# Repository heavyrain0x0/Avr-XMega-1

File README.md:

# Avr-XMega-1
An AVR Xmega Development Board

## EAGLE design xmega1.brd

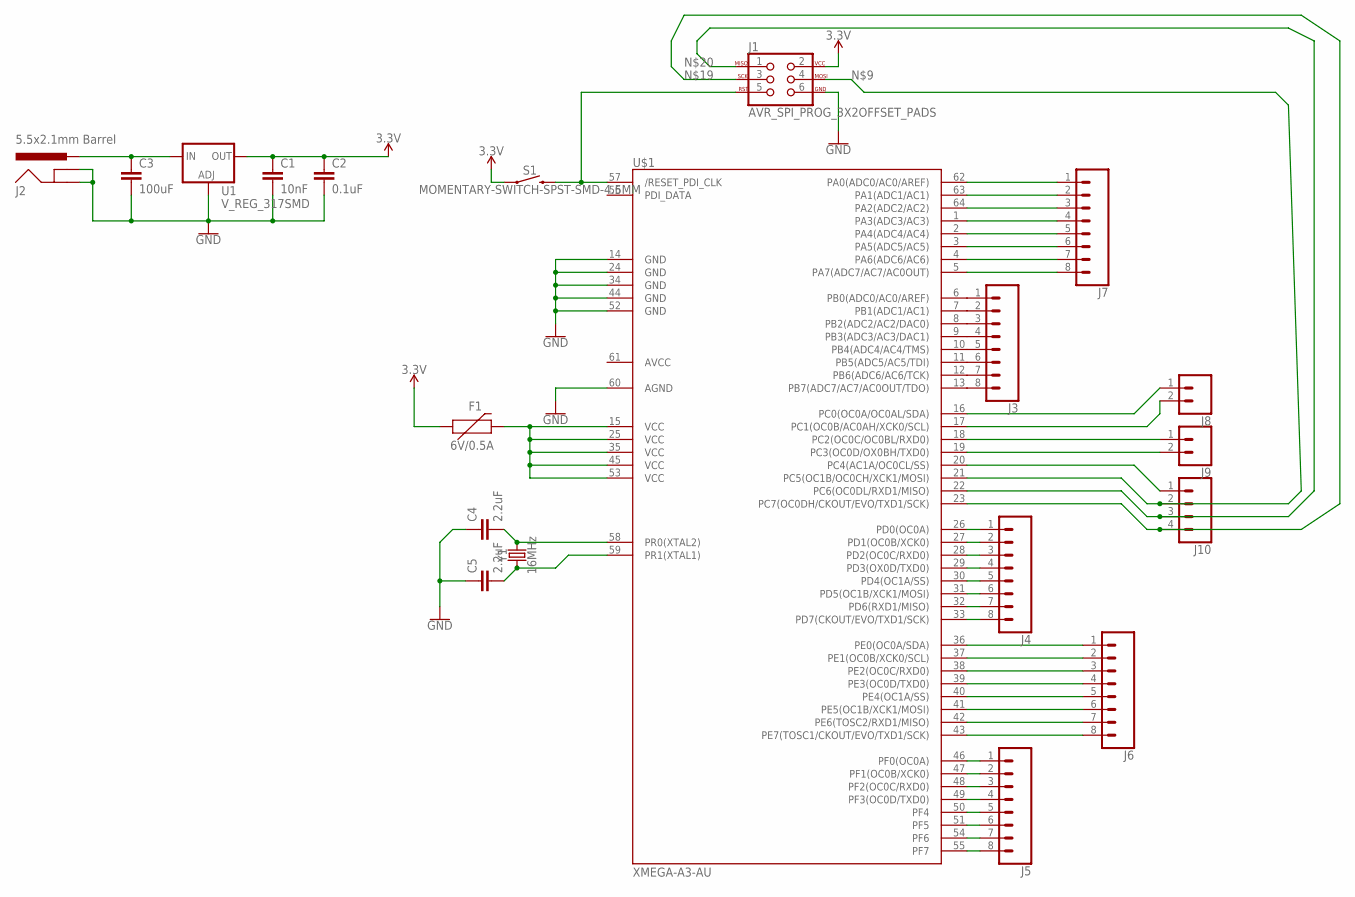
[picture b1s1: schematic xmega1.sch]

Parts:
C1: 10nF; 0603
C2: 0.1uF; 0402-CAP
C3: 100uF; 1210
C4, C5: 2.2uF; 0402-CAP
F1: 6V/0.5A; 1206
J1: AVR_SPI_PROG_3X2OFFSET_PADS; 2X3_OFFSET
J2: 5.5x2.1mm Barrel; POWER_JACK_SMD
J3, J4, J5, J6, J7: CONN_08LONGPADS; 1X08_LONGPADS
J8, J9: CONN_02PTH3; 1X02_LONGPADS
J10: CONN_04LONGPADS; 1X04_LONGPADS
S1: MOMENTARY-SWITCH-SPST-SMD-4.5MM; TACTILE_SWITCH_SMD_4.5MM
U1: V_REG_317SMD; SOT223
U$1: XMEGA-A3-AU; TQFP64_14X14MM_MCU
Y1: 16MHz; CRYSTAL-SMD-5X3.2-4PAD

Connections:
3.3V: C1.1, C2.1, F1.1, J1.2, S1.2 (1), S1.3 (1), U1.2 (OUT)
GND: C1.2, C2.2, C3.2, C4.1, C5.1, J1.6, J2.GND (GNDBREAK), J2.P$4 (GND), U1.1 (ADJ), U$1.14 (GND1), U$1.24 (GND2), U$1.34 (GND3), U$1.44 (GND4), U$1.52 (GND5), U$1.60 (AGND)
unnamed: F1.2, U$1.15 (VCC1), U$1.25 (VCC2), U$1.35 (VCC3), U$1.45 (VCC4), U$1.53 (VCC5)
unnamed: J1.5, S1.1 (2), S1.4 (2), U$1.57 (/RESET_PDI_CLK)
unnamed: J8.1, U$1.16 (PC0(OC0A/OC0AL/SDA))
unnamed: C3.1, J2.VIN0 (PWR), U1.3 (IN)
unnamed: J8.2, U$1.17 (PC1(OC0B/AC0AH/XCK0/SCL))
unnamed: C5.2, U$1.59 (PR1(XTAL1)), Y1.1
unnamed: C4.2, U$1.58 (PR0(XTAL2)), Y1.3 (2)
unnamed: J3.1, U$1.6 (PB0(ADC0/AC0/AREF))
unnamed: J1.4, J10.2, U$1.21 (PC5(OC1B/OC0CH/XCK1/MOSI))
unnamed: J7.1, U$1.62 (PA0(ADC0/AC0/AREF))
unnamed: J7.2, U$1.63 (PA1(ADC1/AC1))
unnamed: J7.3, U$1.64 (PA2(ADC2/AC2))
unnamed: J7.4, U$1.1 (PA3(ADC3/AC3))
unnamed: J7.5, U$1.2 (PA4(ADC4/AC4))
unnamed: J7.6, U$1.3 (PA5(ADC5/AC5))
unnamed: J6.1, U$1.36 (PE0(OC0A/SDA))
unnamed: J6.2, U$1.37 (PE1(OC0B/XCK0/SCL))
unnamed: J9.1, U$1.18 (PC2(OC0C/OC0BL/RXD0))
unnamed: J1.3, J10.4, U$1.23 (PC7(OC0DH/CKOUT/EVO/TXD1/SCK))
unnamed: J1.1, J10.3, U$1.22 (PC6(OC0DL/RXD1/MISO))
unnamed: J9.2, U$1.19 (PC3(OC0D/OX0BH/TXD0))
unnamed: J3.2, U$1.7 (PB1(ADC1/AC1))
unnamed: J3.3, U$1.8 (PB2(ADC2/AC2/DAC0))
unnamed: J3.4, U$1.9 (PB3(ADC3/AC3/DAC1))
unnamed: J3.5, U$1.10 (PB4(ADC4/AC4/TMS))
unnamed: J3.6, U$1.11 (PB5(ADC5/AC5/TDI))
unnamed: J3.7, U$1.12 (PB6(ADC6/AC6/TCK))
unnamed: J3.8, U$1.13 (PB7(ADC7/AC7/AC0OUT/TDO))
unnamed: J7.7, U$1.4 (PA6(ADC6/AC6))
unnamed: J7.8, U$1.5 (PA7(ADC7/AC7/AC0OUT))
unnamed: J4.1, U$1.26 (PD0(OC0A))
unnamed: J4.2, U$1.27 (PD1(OC0B/XCK0))
unnamed: J4.3, U$1.28 (PD2(OC0C/RXD0))
unnamed: J4.4, U$1.29 (PD3(OX0D/TXD0))
unnamed: J4.5, U$1.30 (PD4(OC1A/SS))
unnamed: J4.6, U$1.31 (PD5(OC1B/XCK1/MOSI))
unnamed: J4.7, U$1.32 (PD6(RXD1/MISO))
unnamed: J4.8, U$1.33 (PD7(CKOUT/EVO/TXD1/SCK))
unnamed: J6.3, U$1.38 (PE2(OC0C/RXD0))
unnamed: J6.4, U$1.39 (PE3(OC0D/TXD0))
unnamed: J6.5, U$1.40 (PE4(OC1A/SS))
unnamed: J6.6, U$1.41 (PE5(OC1B/XCK1/MOSI))
unnamed: J6.7, U$1.42 (PE6(TOSC2/RXD1/MISO))
unnamed: J6.8, U$1.43 (PE7(TOSC1/CKOUT/EVO/TXD1/SCK))
unnamed: J5.1, U$1.46 (PF0(OC0A))
unnamed: J5.2, U$1.47 (PF1(OC0B/XCK0))
unnamed: J5.3, U$1.48 (PF2(OC0C/RXD0))
unnamed: J5.4, U$1.49 (PF3(OC0D/TXD0))
unnamed: J5.5, U$1.50 (PF4)
unnamed: J5.6, U$1.51 (PF5)
unnamed: J5.7, U$1.54 (PF6)
unnamed: J5.8, U$1.55 (PF7)
unnamed: J10.1, U$1.20 (PC4(AC1A/OC0CL/SS))

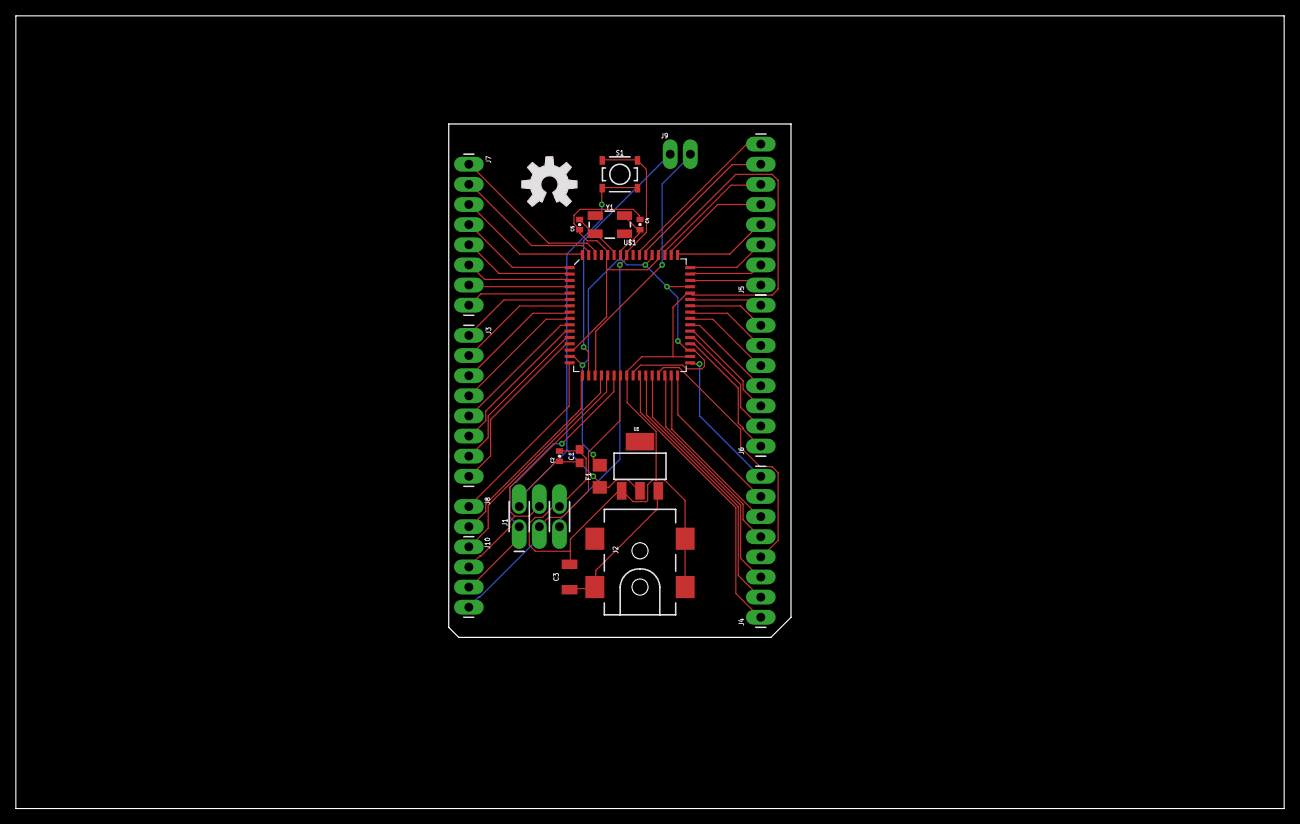
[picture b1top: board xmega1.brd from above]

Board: 2 copper layers, 160.0 x 100.0 mm, 22 parts (0 on the bottom side), 55 nets.

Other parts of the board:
U$2: OSHW-LOGO-L_COPPER
U$3: OSHW-LOGO-L

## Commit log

2017-10-26 Add files via upload
    Initial commit of alpha board design

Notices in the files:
parts and their libraries:
SparkFun-Capacitors: Licensing: Creative Commons ShareAlike 4.0 International - https://creativecommons.org/licenses/by-sa/4.0
